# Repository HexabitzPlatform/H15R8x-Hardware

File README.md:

# H15R8x-Hardware
Hexabitz Hi-precision Voltage & Current Analog Output Module Hardware Design

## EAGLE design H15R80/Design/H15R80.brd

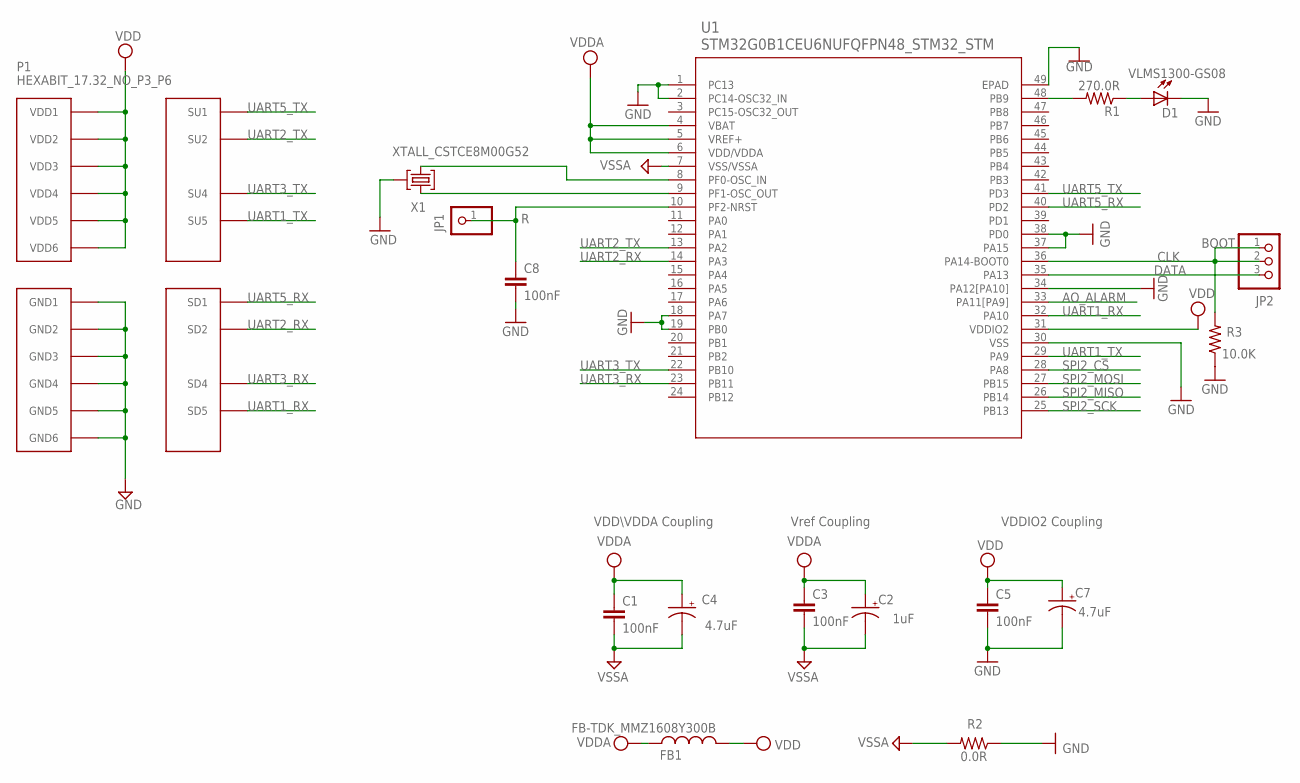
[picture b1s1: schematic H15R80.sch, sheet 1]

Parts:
C1: 100nF; C-0603; TOLERANCE 10%; VOLTAGE_RATING 50V; MPN C0603C103K5RACTU
C2: 1uF; C-0805-POL; TOLERANCE 10%; VOLTAGE_RATING 25V; MPN GRM21BC81E475KA12L
C3, C8: 100nF; C-0603; TOLERANCE 10%; VOLTAGE_RATING 10V; MPN C0603C104K8RACTU
C4: 4.7uF; C-0805-POL; TOLERANCE 10%; VOLTAGE_RATING 16V; MPN CC0805KKX7R7BB105
C5: 100nF; C-0603; TOLERANCE 10%; VOLTAGE_RATING 10; MPN C0603C104K8RACTU
C7: 4.7uF; C-0805-POL; TOLERANCE 10%; VOLTAGE_RATING 25V; MPN GRM21BC81E475KA12L
D1: VLMS1300-GS08; MPN VLMS1300-GS08
FB1: FB-TDK_MMZ1608Y300B; MPN MMZ1608Y300B
JP1: R; 1X01
JP2: PINHD-1X3; 1X03
P1: HEXABIT_17.32_NO_P3_P6
R1: 270.0R; R-0603; TOLERANCE 1%; MPN RC0603FR-07270RL
R2: 0.0R; R-0603; MPN RC0603JR-070RL
R3: 10.0K; R-0603; TOLERANCE 5%; MPN RC0603JR-0710KL
U1: STM32G0B1CEU6NUFQFPN48_STM32_STM; UFQFPN48_STM32_STM
X1: XTALL_CSTCE8M00G52

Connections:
AO_ALARM: U1.33 (PA11[PA9]); also elsewhere on the board
CLK: JP2.1, JP2.2, R3.2, U1.36 (PA14-BOOT0)
DATA: JP2.3, U1.35 (PA13)
GND: C5.2, C7.2 (-), C8.2, D1.C, P1.PAD_PD7 (GND1), P1.PAD_PD8 (GND2), P1.PAD_PD9 (GND3), P1.PAD_PD10 (GND4), P1.PAD_PD11 (GND5), P1.PAD_PD12 (GND6), R2.1, R3.1, U1.1 (PC13), U1.2 (PC14-OSC32_IN), U1.18 (PA7), U1.19 (PB0), U1.30 (VSS), U1.34 (PA12[PA10]), U1.37 (PA15), U1.38 (PD0), U1.49 (EPAD), X1.P$2 (2)
unnamed: R1.2, U1.48 (PB9)
unnamed: D1.A, R1.1
unnamed: C8.1, JP1.1, U1.10 (PF2-NRST)
unnamed: U1.9 (PF1-OSC_OUT), X1.P$1 (1)
unnamed: U1.8 (PF0-OSC_IN), X1.P$3 (3)
SPI2_CS: U1.28 (PA8); also elsewhere on the board
SPI2_MISO: U1.26 (PB14); also elsewhere on the board
SPI2_MOSI: U1.27 (PB15); also elsewhere on the board
SPI2_SCK: U1.25 (PB13); also elsewhere on the board
UART1_RX: P1.PAD_PD5 (SD5), U1.32 (PA10)
UART1_TX: P1.PAD_PU5 (SU5), U1.29 (PA9)
UART2_RX: P1.PAD_PD2 (SD2), U1.14 (PA3)
UART2_TX: P1.PAD_PU2 (SU2), U1.13 (PA2)
UART3_RX: P1.PAD_PD4 (SD4), U1.23 (PB11)
UART3_TX: P1.PAD_PU4 (SU4), U1.22 (PB10)
UART5_RX: P1.PAD_PD1 (SD1), U1.40 (PD2)
UART5_TX: P1.PAD_PU1 (SU1), U1.41 (PD3)
VDD: C5.1, C7.1 (+), FB1.2, P1.PAD_PU7 (VDD1), P1.PAD_PU8 (VDD2), P1.PAD_PU9 (VDD3), P1.PAD_PU10 (VDD4), P1.PAD_PU11 (VDD5), P1.PAD_PU12 (VDD6), U1.31 (VDDIO2)
VDDA: C1.1, C2.1 (+), C3.1, C4.1 (+), FB1.1, U1.4 (VBAT), U1.5 (VREF+), U1.6 (VDD/VDDA); also elsewhere on the board
VSSA: C1.2, C2.2 (-), C3.2, C4.2 (-), R2.2, U1.7 (VSS/VSSA); also elsewhere on the board

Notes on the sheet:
VDD\VDDA Coupling
Vref Coupling
VDDIO2 Coupling
BOOT

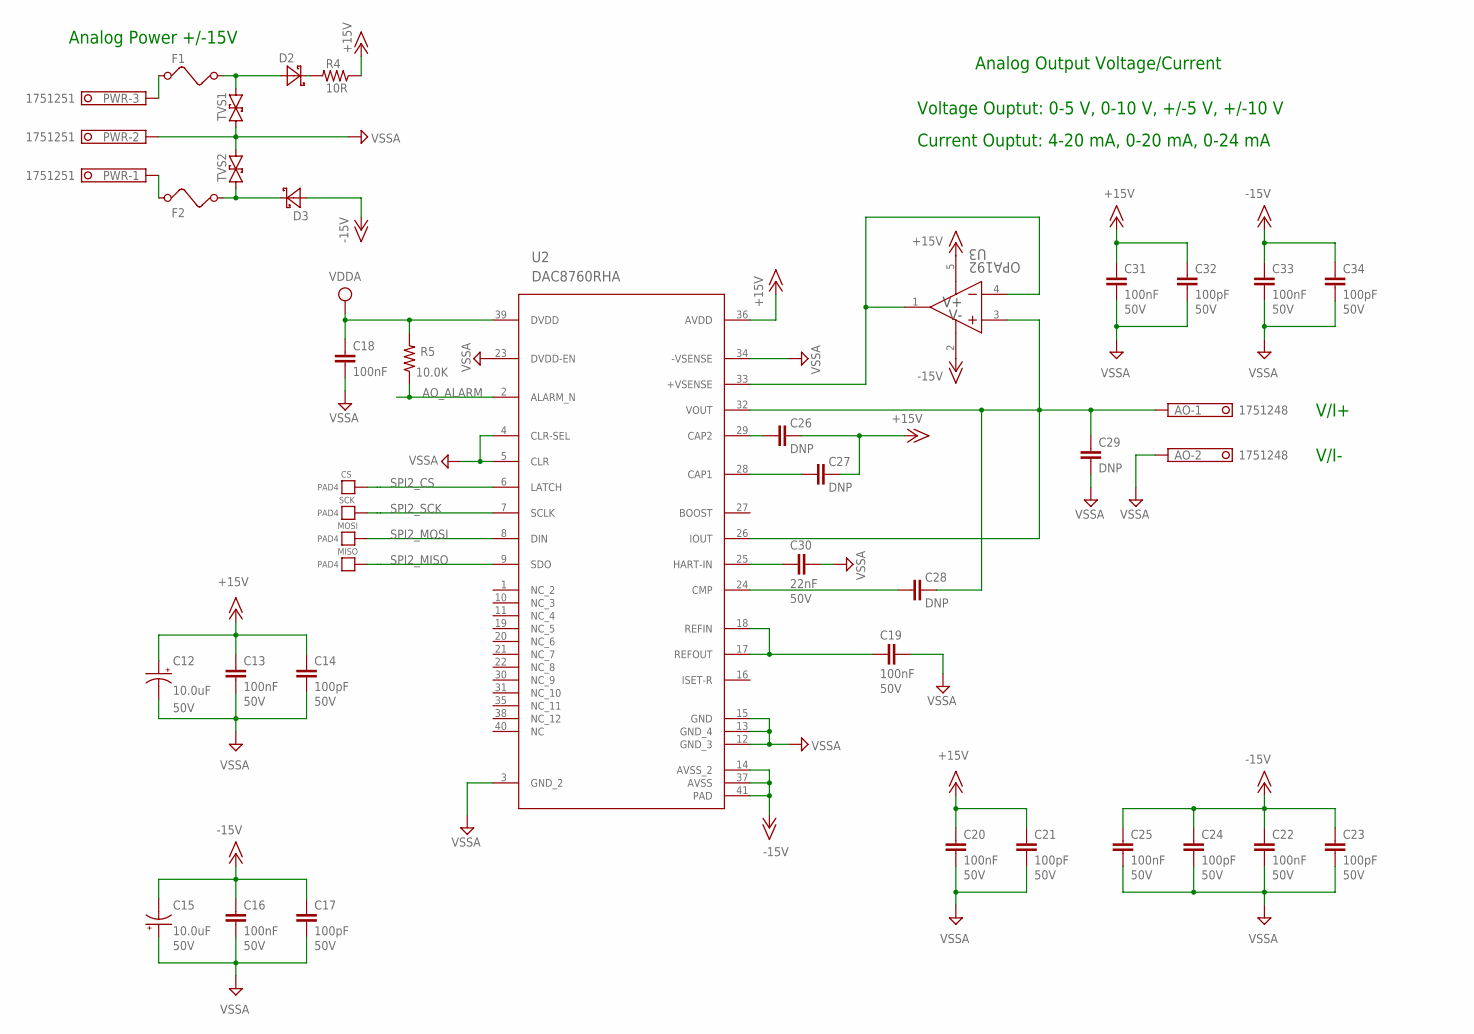
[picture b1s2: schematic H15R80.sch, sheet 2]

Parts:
AO: 1751248; MPN 1751248
C12, C15: 10.0uF; CT7343; VOLTAGE 50V; MPN T491D106K050AT
C13, C16, C19, C20, C22, C25, C31, C33: 100nF; C-0603; TOLERANCE 10%; VOLTAGE_RATING 50V; MPN CL10B104KB8NNNC
C14, C17, C21, C23, C24, C32, C34: 100pF; C-0603; TOLERANCE 10%; VOLTAGE_RATING 50V; MPN 06035A101JAT2A
C18: 100nF; C-0603; TOLERANCE 10%; VOLTAGE_RATING 10V; MPN C0603C104K8RACTU
C26, C27, C28, C29: DNP; C-0603; MPN DNP
C30: 22nF; C-0603; TOLERANCE 10%; VOLTAGE_RATING 50V; MPN C1608X7R1H223K080AA
CS: PAD4
D2, D3: DIOD-SOD-123; SOD123
F1, F2: NANOSMDC035F-2120; R1206
MISO: PAD4
MOSI: PAD4
PWR: 1751251; MPN 1751251
R4: 10R; R-0603; TOLERANCE 5%; MPN RC0603JR-0710KL
R5: 10.0K; R-0603; TOLERANCE 5%; MPN RC0603JR-0710KL
SCK: PAD4
TVS1, TVS2: SMBJ30CA; DO214AA
U2: DAC8760RHA; RHA0040A
U3: OPA192; DBV0005A_N; MPN OPA192IDBVR

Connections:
+15V: C12.+, C13.1, C14.1, C20.1, C21.1, C26.2, C27.2, C31.1, C32.1, R4.1, U2.36 (AVDD), U3.5 (V+)
-15V: C15.-, C16.1, C17.1, C22.1, C23.1, C24.1, C25.1, C33.1, C34.1, D3.1 (A), U2.14 (AVSS_2), U2.37 (AVSS), U2.41 (PAD), U3.2 (V-)
AO_ALARM: R5.1, U2.2 (ALARM_N); also elsewhere on the board
unnamed: AO.1, C28.2, C29.2, U2.26 (IOUT), U2.32 (VOUT), U3.3 (IN+)
unnamed: C19.1, U2.17 (REFOUT), U2.18 (REFIN)
unnamed: C26.1, U2.29 (CAP2)
unnamed: F1.1, PWR.3
unnamed: C27.1, U2.28 (CAP1)
unnamed: C28.1, U2.24 (CMP)
unnamed: F2.1, PWR.1
unnamed: U2.33 (+VSENSE), U3.1 (OUT), U3.4 (IN-)
unnamed: C30.1, U2.25 (HART-IN)
unnamed: D3.2 (C), F2.2, TVS2.A (1)
unnamed: D2.1 (A), F1.2, TVS1.C (2)
unnamed: D2.2 (C), R4.2
SPI2_CS: CS.P$1, U2.6 (LATCH); also elsewhere on the board
SPI2_MISO: MISO.P$1, U2.9 (SDO); also elsewhere on the board
SPI2_MOSI: MOSI.P$1, U2.8 (DIN); also elsewhere on the board
SPI2_SCK: SCK.P$1, U2.7 (SCLK); also elsewhere on the board
VDDA: C18.1, R5.2, U2.39 (DVDD); also elsewhere on the board
VSSA: AO.2, C12.-, C13.2, C14.2, C15.+, C16.2, C17.2, C18.2, C19.2, C20.2, C21.2, C22.2, C23.2, C24.2, C25.2, C29.1, C30.2, C31.2, C32.2, C33.2, C34.2, PWR.2, TVS1.A (1), TVS2.C (2), U2.3 (GND_2), U2.4 (CLR-SEL), U2.5 (CLR), U2.12 (GND_3), U2.13 (GND_4), U2.15 (GND), U2.23 (DVDD-EN), U2.34 (-VSENSE); also elsewhere on the board

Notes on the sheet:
Analog Power +/-15V
Analog Output Voltage/Current
Voltage Ouptut: 0-5 V, 0-10 V, +/-5 V, +/-10 V
Current Ouptut: 4-20 mA, 0-20 mA, 0-24 mA
V/I+
V/I-

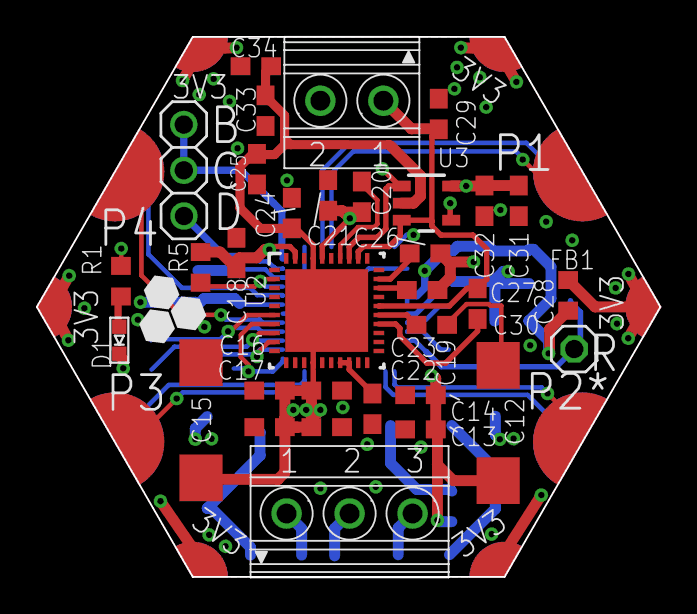
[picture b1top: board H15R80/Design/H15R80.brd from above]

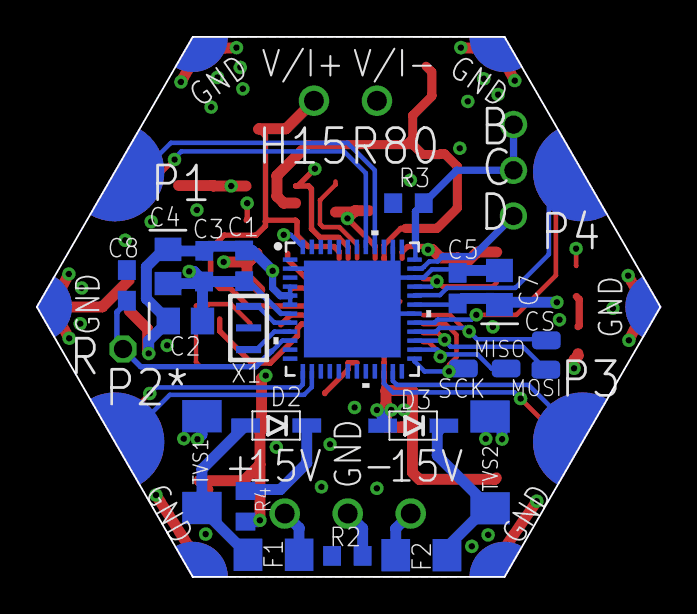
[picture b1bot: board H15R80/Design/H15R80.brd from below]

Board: 4 copper layers, 34.6 x 30.0 mm, 56 parts (22 on the bottom side), 38 nets.

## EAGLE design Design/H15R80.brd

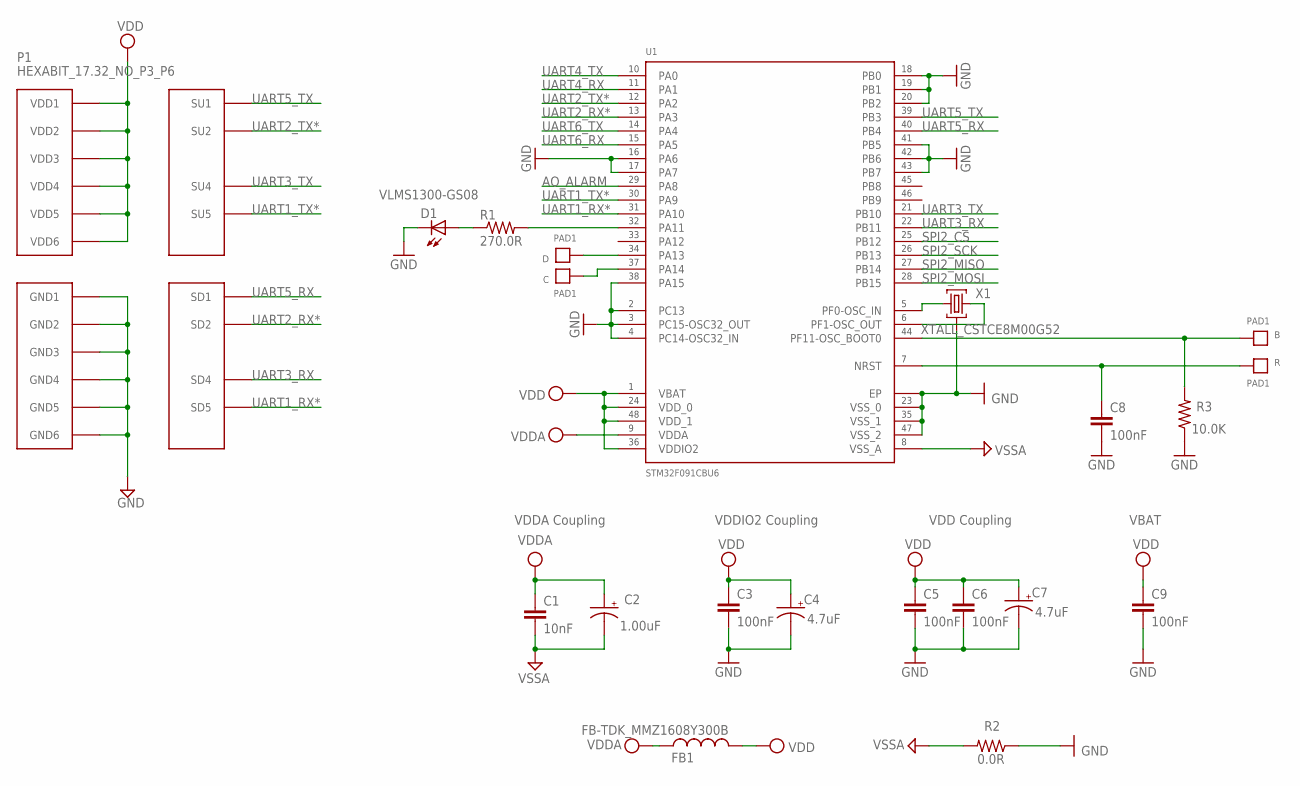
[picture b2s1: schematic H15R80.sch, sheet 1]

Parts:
B: PAD1
C: PAD1
C1: 10nF; C-0603; TOLERANCE 10%; VOLTAGE_RATING 50V; MPN C0603C103K5RACTU
C2: 1.00uF; C-0805-POL; TOLERANCE 10%; VOLTAGE_RATING 16V; MPN CC0805KKX7R7BB105
C3, C6, C8: 100nF; C-0603; TOLERANCE 10%; VOLTAGE_RATING 10V; MPN C0603C104K8RACTU
C4, C7: 4.7uF; C-0805-POL; TOLERANCE 10%; VOLTAGE_RATING 25V; MPN GRM21BC81E475KA12L
C5: 100nF; C-0603; TOLERANCE 10%; VOLTAGE_RATING 10; MPN C0603C104K8RACTU
C9: 100nF; C-0603; TOLERANCE 10V; VOLTAGE_RATING 10%; MPN C0603C104K8RACTU
D: PAD1
D1: VLMS1300-GS08; MPN VLMS1300-GS08
FB1: FB-TDK_MMZ1608Y300B; MPN MMZ1608Y300B
P1: HEXABIT_17.32_NO_P3_P6
R: PAD1
R1: 270.0R; R-0603; TOLERANCE 1%; MPN RC0603FR-07270RL
R2: 0.0R; R-0603; MPN RC0603JR-070RL
R3: 10.0K; R-0603; TOLERANCE 5%; MPN RC0603JR-0710KL
U1: STM32F091CBU6
X1: XTALL_CSTCE8M00G52

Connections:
AO_ALARM: U1.P$29 (PA8); also elsewhere on the board
B1: B.P$1, B.P$2, R3.2, U1.P$44 (PF11-OSC_BOOT0)
GND: C3.2, C4.2 (-), C5.2, C6.2, C7.2 (-), C8.2, C9.2, D1.C, P1.PAD_PD7 (GND1), P1.PAD_PD8 (GND2), P1.PAD_PD9 (GND3), P1.PAD_PD10 (GND4), P1.PAD_PD11 (GND5), P1.PAD_PD12 (GND6), R2.1, R3.1, U1.EP, U1.P$2 (PC13), U1.P$3 (PC14-OSC32_IN), U1.P$4 (PC15-OSC32_OUT), U1.P$16 (PA6), U1.P$17 (PA7), U1.P$18 (PB0), U1.P$19 (PB1), U1.P$20 (PB2), U1.P$23 (VSS_0), U1.P$35 (VSS_1), U1.P$38 (PA15), U1.P$41 (PB5), U1.P$42 (PB6), U1.P$43 (PB7), U1.P$47 (VSS_2), X1.P$2 (2)
unnamed: R1.2, U1.P$32 (PA11)
unnamed: D1.A, R1.1
unnamed: U1.P$5 (PF0-OSC_IN), X1.P$1 (1)
unnamed: U1.P$6 (PF1-OSC_OUT), X1.P$3 (3)
unnamed: D.P$1, D.P$2, U1.P$34 (PA13)
unnamed: C.P$1, C.P$2, U1.P$37 (PA14)
R1: C8.1, R.P$1, R.P$2, U1.P$7 (NRST)
SPI2_CS: U1.P$25 (PB12); also elsewhere on the board
SPI2_MISO: U1.P$27 (PB14); also elsewhere on the board
SPI2_MOSI: U1.P$28 (PB15); also elsewhere on the board
SPI2_SCK: U1.P$26 (PB13); also elsewhere on the board
UART1_RX*: P1.PAD_PD5 (SD5), U1.P$31 (PA10)
UART1_TX*: P1.PAD_PU5 (SU5), U1.P$30 (PA9)
UART2_RX*: P1.PAD_PD2 (SD2), U1.P$13 (PA3)
UART2_TX*: P1.PAD_PU2 (SU2), U1.P$12 (PA2)
UART3_RX: P1.PAD_PD4 (SD4), U1.P$22 (PB11)
UART3_TX: P1.PAD_PU4 (SU4), U1.P$21 (PB10)
UART4_RX: U1.P$11 (PA1)
UART4_TX: U1.P$10 (PA0)
UART5_RX: P1.PAD_PD1 (SD1), U1.P$40 (PB4)
UART5_TX: P1.PAD_PU1 (SU1), U1.P$39 (PB3)
UART6_RX: U1.P$15 (PA5)
UART6_TX: U1.P$14 (PA4)
VDD: C3.1, C4.1 (+), C5.1, C6.1, C7.1 (+), C9.1, FB1.2, P1.PAD_PU7 (VDD1), P1.PAD_PU8 (VDD2), P1.PAD_PU9 (VDD3), P1.PAD_PU10 (VDD4), P1.PAD_PU11 (VDD5), P1.PAD_PU12 (VDD6), U1.P$1 (VBAT), U1.P$24 (VDD_0), U1.P$36 (VDDIO2), U1.P$48 (VDD_1)
VDDA: C1.1, C2.1 (+), FB1.1, U1.P$9 (VDDA); also elsewhere on the board
VSSA: C1.2, C2.2 (-), R2.2, U1.P$8 (VSS_A); also elsewhere on the board

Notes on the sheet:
VDDA Coupling
VDDIO2 Coupling
VDD Coupling
VBAT

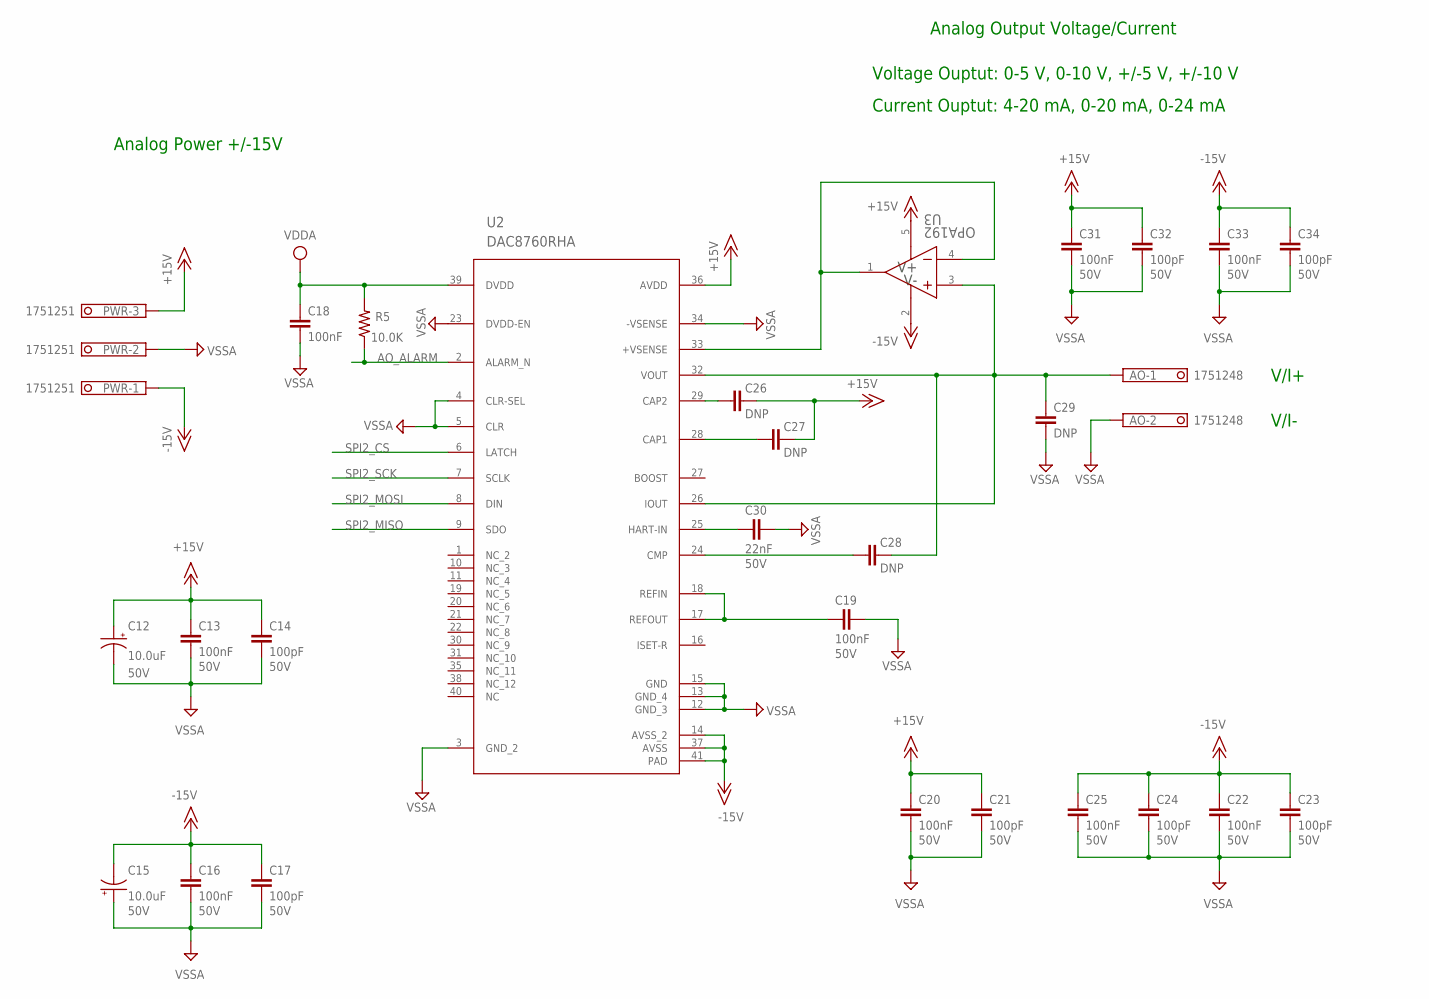
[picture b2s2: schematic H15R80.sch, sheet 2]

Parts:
AO: 1751248; MPN 1751248
C12, C15: 10.0uF; CT7343; VOLTAGE 50V; MPN T491D106K050AT
C13, C16, C19, C20, C22, C25, C31, C33: 100nF; C-0603; TOLERANCE 10%; VOLTAGE_RATING 50V; MPN CL10B104KB8NNNC
C14, C17, C21, C23, C24, C32, C34: 100pF; C-0603; TOLERANCE 10%; VOLTAGE_RATING 50V; MPN 06035A101JAT2A
C18: 100nF; C-0603; TOLERANCE 10%; VOLTAGE_RATING 10V; MPN C0603C104K8RACTU
C26, C27, C28, C29: DNP; C-0603; MPN DNP
C30: 22nF; C-0603; TOLERANCE 10%; VOLTAGE_RATING 50V; MPN C1608X7R1H223K080AA
PWR: 1751251; MPN 1751251
R5: 10.0K; R-0603; TOLERANCE 5%; MPN RC0603JR-0710KL
U2: DAC8760RHA; RHA0040A
U3: OPA192; DBV0005A_N; MPN OPA192IDBVR

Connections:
+15V: C12.+, C13.1, C14.1, C20.1, C21.1, C26.2, C27.2, C31.1, C32.1, PWR.3, U2.36 (AVDD), U3.5 (V+)
-15V: C15.-, C16.1, C17.1, C22.1, C23.1, C24.1, C25.1, C33.1, C34.1, PWR.1, U2.14 (AVSS_2), U2.37 (AVSS), U2.41 (PAD), U3.2 (V-)
AO_ALARM: R5.1, U2.2 (ALARM_N); also elsewhere on the board
unnamed: AO.1, C28.2, C29.2, U2.26 (IOUT), U2.32 (VOUT), U3.3 (IN+)
unnamed: C19.1, U2.17 (REFOUT), U2.18 (REFIN)
unnamed: C26.1, U2.29 (CAP2)
unnamed: C27.1, U2.28 (CAP1)
unnamed: C28.1, U2.24 (CMP)
unnamed: U2.33 (+VSENSE), U3.1 (OUT), U3.4 (IN-)
unnamed: C30.1, U2.25 (HART-IN)
SPI2_CS: U2.6 (LATCH); also elsewhere on the board
SPI2_MISO: U2.9 (SDO); also elsewhere on the board
SPI2_MOSI: U2.8 (DIN); also elsewhere on the board
SPI2_SCK: U2.7 (SCLK); also elsewhere on the board
VDDA: C18.1, R5.2, U2.39 (DVDD); also elsewhere on the board
VSSA: AO.2, C12.-, C13.2, C14.2, C15.+, C16.2, C17.2, C18.2, C19.2, C20.2, C21.2, C22.2, C23.2, C24.2, C25.2, C29.1, C30.2, C31.2, C32.2, C33.2, C34.2, PWR.2, U2.3 (GND_2), U2.4 (CLR-SEL), U2.5 (CLR), U2.12 (GND_3), U2.13 (GND_4), U2.15 (GND), U2.23 (DVDD-EN), U2.34 (-VSENSE); also elsewhere on the board

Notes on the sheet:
Analog Power +/-15V
Analog Output Voltage/Current
Voltage Ouptut: 0-5 V, 0-10 V, +/-5 V, +/-10 V
Current Ouptut: 4-20 mA, 0-20 mA, 0-24 mA
V/I+
V/I-

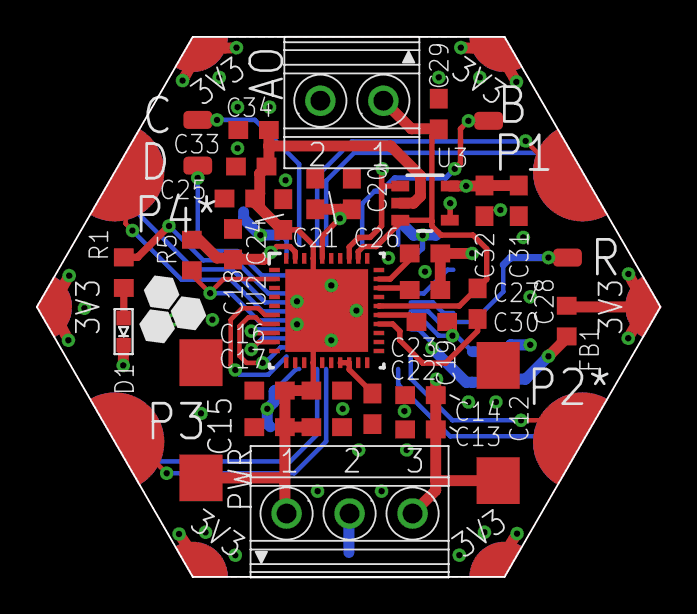
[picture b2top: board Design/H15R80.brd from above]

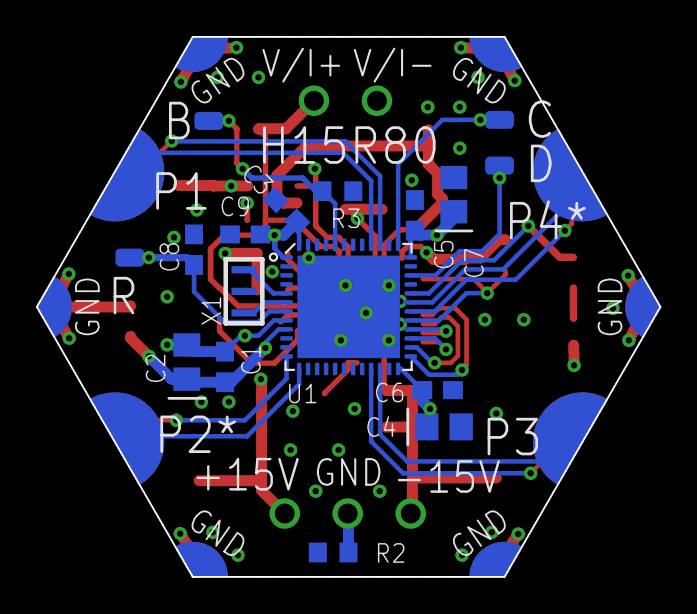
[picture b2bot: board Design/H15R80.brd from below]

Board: 4 copper layers, 34.6 x 30.0 mm, 49 parts (13 on the bottom side), 34 nets.

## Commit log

2019-12-20 Generated template files Added connectors and DAC component
2019-12-21 Finished schematics
2019-12-23 Placed most components Routed analog routes
2019-12-24 Routing digital section
2019-12-30 Finished routing and silkscreen placement
2020-01-01 Solved DRC
2020-01-01 Added schematics PDF, drill, gerber, pick n place files
2020-01-01 Added BOM. Release V0
2020-02-15 Adding stack file
2022-11-09 Changing MCU to STM32G0
2023-02-16 Replace the blind vias with through hole ones
2023-02-16 -Correcting some documentaion issues

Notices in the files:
parts and their libraries:
COPYRIGHT: Copyright (C) 2022 Ultra Librarian. All rights reserved.
